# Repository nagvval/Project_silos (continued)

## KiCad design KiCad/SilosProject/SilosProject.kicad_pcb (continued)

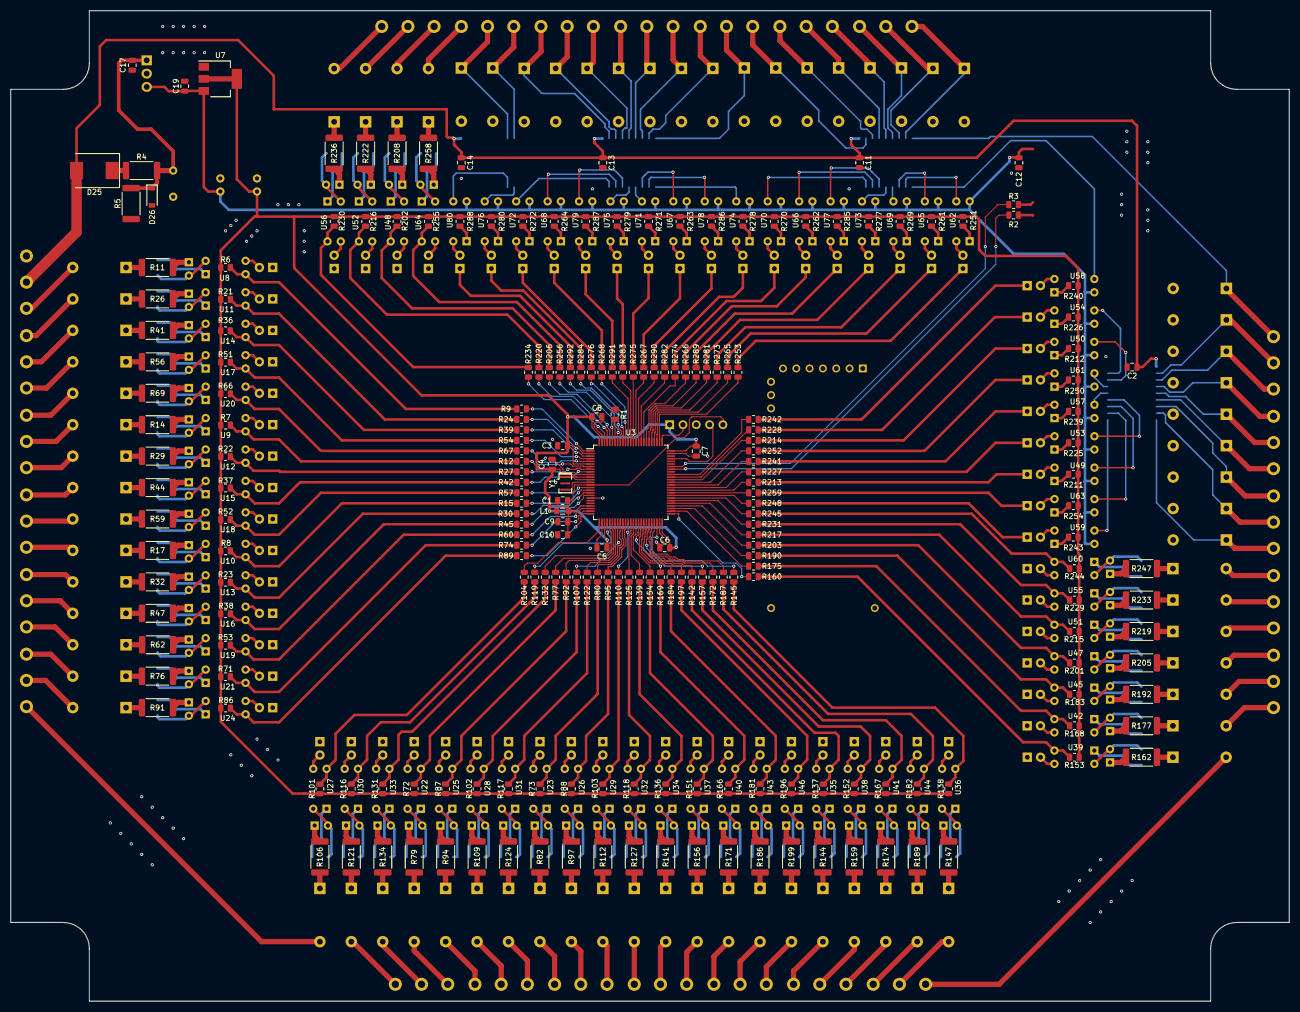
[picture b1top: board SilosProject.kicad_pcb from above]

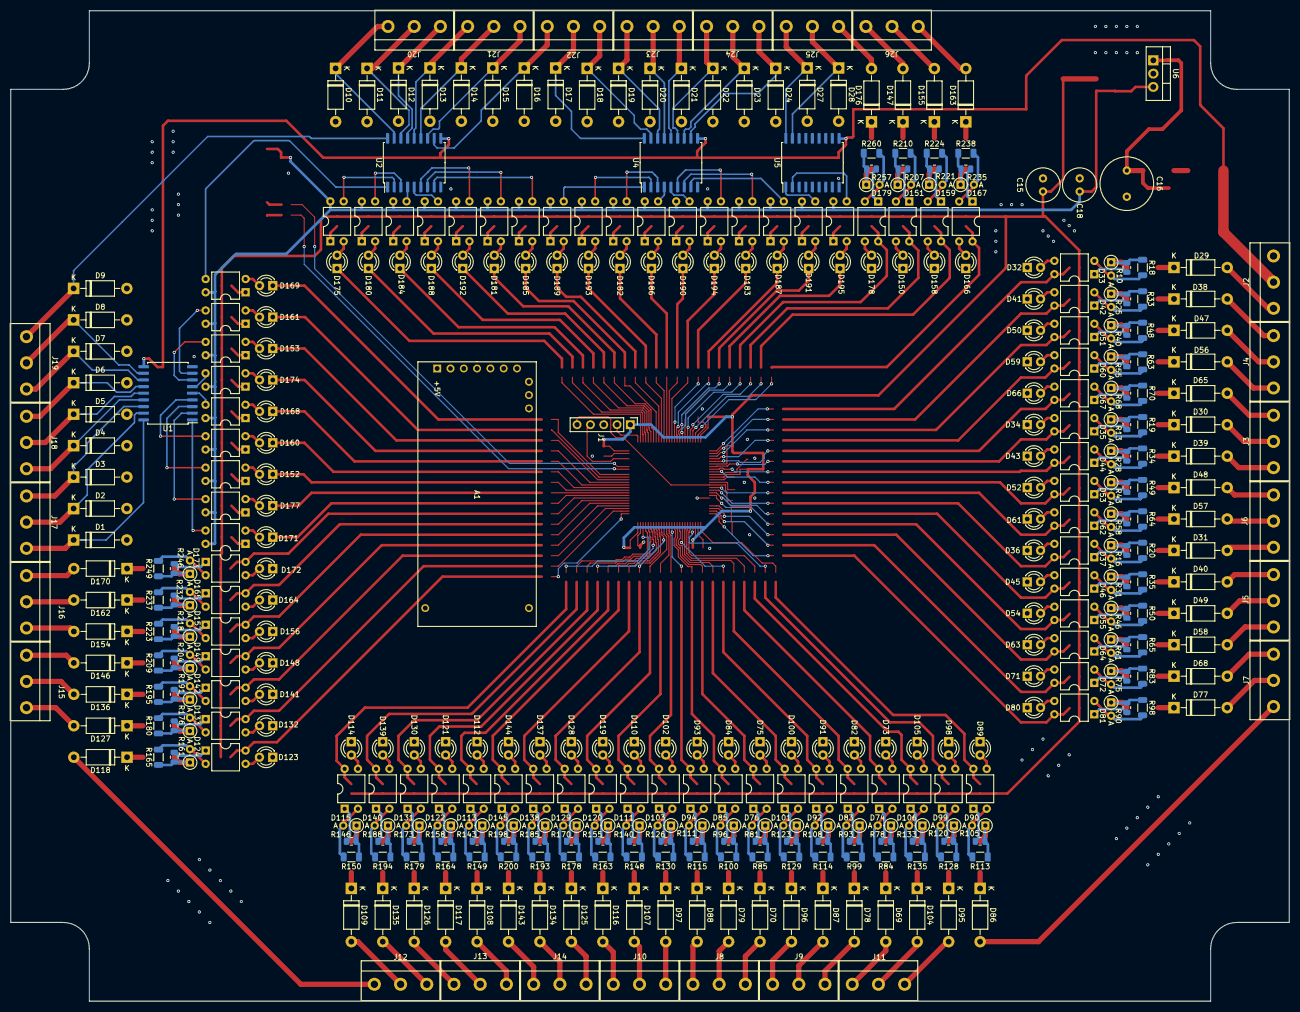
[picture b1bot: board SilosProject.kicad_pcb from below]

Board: 2 copper layers, 244.0 x 189.0 mm, 615 parts (395 on the bottom side), 548 nets.

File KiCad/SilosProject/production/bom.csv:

Designator,Footprint,Quantity,Value,LCSC Part #
A1,USR-TCP232-T2_MODUL,1,USR-TCP232-T2,
"C1, C11, C12, C13, C14, C17, C19, C2, C4, C5, C6, C7, C8",C_0805_2012Metric,13,100nF,
C10,C_0805_2012Metric,1,10nF,
C15,C_Radial_D6.3mm_H11.0mm_P2.50mm,1,"220uF, 10V",
C16,C_Radial_D10.0mm_H12.5mm_P5.00mm,1,220uF 50V,
C18,C_Radial_D6.3mm_H11.0mm_P2.50mm,1,220uF 25V,
C3,C_0805_2012Metric,1,4.7uF,
C9,C_0805_2012Metric,1,1uF,
"D1, D10, D104, D107, D108, D109, D11, D116, D117, D118, D12, D125, D126, D127, D13, D134, D135, D136, D14, D143, D146, D147, D15, D154, D155, D16, D162, D163, D17, D170, D176, D18, D19, D2, D20, D21, D22, D23, D24, D27, D28, D29, D3, D30, D31, D38, D39, D4, D40, D47, D48, D49, D5, D56, D57, D58, D6, D65, D68, D69, D7, D70, D77, D78, D79, D8, D86, D87, D88, D9, D95, D96, D97",D_DO-41_SOD81_P10.16mm_Horizontal,73,1N4007,
"D100, D102, D105, D110, D112, D114, D119, D121, D123, D128, D130, D132, D137, D139, D141, D144, D148, D150, D152, D153, D156, D158, D160, D161, D164, D166, D168, D169, D171, D172, D174, D175, D177, D178, D180, D181, D182, D183, D184, D185, D186, D187, D188, D189, D190, D191, D192, D193, D194, D195, D32, D34, D36, D41, D43, D45, D50, D52, D54, D59, D61, D63, D66, D73, D75, D80, D82, D84, D89, D91, D93, D98",LED_D3.0mm,72,LED_GREEN_3mm,
"D101, D103, D106, D111, D113, D115, D120, D122, D124, D129, D131, D133, D138, D140, D142, D145, D149, D151, D157, D159, D165, D167, D173, D179, D33, D35, D37, D42, D44, D46, D51, D53, D55, D60, D62, D64, D67, D72, D74, D76, D81, D83, D85, D90, D92, D94, D99",D_DO-35_SOD27_P2.54mm_Vertical_AnodeUp,47,BZX55-C5V1,
D25,D_SMC,1,S5M,
D26,D_SOD-123,1,BZX55-C7V5,
D71,LED_D3.0mm_IRBlack,1,IR204A,
J1,PinHeader_1x05_P2.54mm_Vertical,1,Screw_Terminal_01x05,
J10,DG306-5.0-03P-12-00A,1,PORT10,
J11,DG306-5.0-03P-12-00A,1,PORT07,
J12,DG306-5.0-03P-12-00A,1,PORT13,
J13,DG306-5.0-03P-12-00A,1,PORT12,
J14,DG306-5.0-03P-12-00A,1,PORT11,
J15,DG306-5.0-03P-12-00A,1,PORT14,
J16,DG306-5.0-03P-12-00A,1,PORT15,
J17,DG306-5.0-03P-12-00A,1,PORT16,
J18,DG306-5.0-03P-12-00A,1,PORT17,
J19,DG306-5.0-03P-12-00A,1,PORT18,
J2,DG306-5.0-03P-12-00A,1,PORT01,
J20,DG306-5.0-03P-12-00A,1,PORT19,
J21,DG306-5.0-03P-12-00A,1,PORT20,
J22,DG306-5.0-03P-12-00A,1,PORT21,
J23,DG306-5.0-03P-12-00A,1,PORT22,
J24,DG306-5.0-03P-12-00A,1,PORT23,
J25,DG306-5.0-03P-12-00A,1,PORT24,
J26,DG306-5.0-03P-12-00A,1,PORT25,
J3,DG306-5.0-03P-12-00A,1,PORT03,
J4,DG306-5.0-03P-12-00A,1,PORT02,
J5,DG306-5.0-03P-12-00A,1,PORT05,
J6,DG306-5.0-03P-12-00A,1,PORT04,
J7,DG306-5.0-03P-12-00A,1,PORT06,
J8,DG306-5.0-03P-12-00A,1,PORT09,
J9,DG306-5.0-03P-12-00A,1,PORT08,
L1,L_0805_2012Metric_Pad1.05x1.20mm_HandSolder,1,100MHz-600,
R1,C_0805_2012Metric,1,10K,
"R10, R105, R108, R111, R120, R123, R126, R13, R133, R140, R143, R146, R155, R158, R16, R161, R170, R173, R176, R185, R188, R191, R198, R204, R207, R218, R221, R232, R235, R246, R25, R257, R28, R31, R40, R43, R46, R55, R58, R61, R68, R75, R78, R81, R90, R93, R96",R_0805_2012Metric,47,200,
"R100, R113, R114, R115, R128, R129, R130, R135, R148, R149, R150, R163, R164, R165, R178, R179, R18, R180, R19, R193, R194, R195, R20, R200, R209, R210, R223, R224, R237, R238, R249, R260, R33, R34, R35, R48, R49, R50, R63, R64, R65, R70, R83, R84, R85, R98, R99",R_1206_3216Metric,47,3.3K,
"R101, R102, R103, R116, R117, R118, R131, R136, R137, R138, R151, R152, R153, R166, R167, R168, R181, R182, R183, R196, R201, R202, R21, R215, R216, R22, R229, R23, R230, R244, R255, R36, R37, R38, R51, R52, R53, R6, R66, R7, R71, R72, R73, R8, R86, R87, R88",R_0805_2012Metric,47,10K,
"R104, R107, R110, R119, R12, R122, R125, R132, R139, R142, R145, R15, R154, R157, R160, R169, R172, R175, R184, R187, R190, R197, R2, R203, R206, R213, R214, R217, R220, R227, R228, R231, R234, R24, R241, R242, R245, R248, R252, R253, R256, R259, R265, R266, R267, R268, R27, R273, R274, R275, R276, R281, R282, R283, R284, R289, R290, R291, R292, R3, R30, R39, R42, R45, R54, R57, R60, R67, R74, R77, R80, R89, R9, R92, R95",R_0805_2012Metric,75,0,
"R106, R109, R11, R112, R121, R124, R127, R134, R14, R141, R144, R147, R156, R159, R162, R17, R171, R174, R177, R186, R189, R192, R199, R205, R208, R219, R222, R233, R236, R247, R258, R26, R29, R32, R41, R44, R47, R56, R59, R62, R69, R76, R79, R82, R91, R94, R97",R_2512_6332Metric,47,10K,
"R211, R212, R225, R226, R239, R240, R243, R250, R251, R254, R261, R262, R263, R264, R269, R270, R271, R272, R277, R278, R279, R280, R285, R286, R287, R288",R_0805_2012Metric,26,1K,
R4,R_2512_6332Metric,1,100K,
R5,R_2512_6332Metric,1,47K,
"U1, U2, U4, U5",SOIC-18W_7.5x11.6mm_P1.27mm,4,ULN2803A,
"U10, U11, U12, U13, U14, U15, U16, U17, U18, U19, U20, U21, U22, U23, U24, U25, U26, U27, U28, U29, U30, U31, U32, U33, U34, U35, U36, U37, U38, U39, U40, U41, U42, U43, U44, U45, U46, U47, U48, U51, U52, U55, U56, U60, U64, U8, U9",DIP-4_W7.62mm,47,EL817,
U3,LQFP-100_14x14mm_P0.5mm,1,STM32F100VETx,
"U49, U50, U53, U54, U57, U58, U59, U61, U62, U63, U65, U66, U67, U68, U69, U70, U71, U72, U73, U74, U75, U76, U77, U78, U79, U80",DIP-4_W7.62mm,26,PC817,
U6,TO-220-3_Vertical,1,L7805,
U7,SOT-223-3_TabPin2,1,LD1117S33TR_SOT223,
Y1,Resonator_SMD_Murata_CSTxExxV-3Pin_3.0x1.1mm,1,8MHz,

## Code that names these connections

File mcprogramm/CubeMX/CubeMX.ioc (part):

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Mcu.Name=STM32F100V(C-D-E)Tx
Mcu.Package=LQFP100
Mcu.UserName=STM32F100VETx
PA0-WKUP.GPIOParameters=GPIO_Label
PA0-WKUP.GPIO_Label=SUM M3
PA0-WKUP.Signal=GPIO_Input
PA1.GPIOParameters=GPIO_Label
PA1.GPIO_Label=SUM M5
PA1.Signal=GPIO_Input
PA10.Mode=Asynchronous
PA10.Signal=USART1_RX
PA13.Signal=SYS_JTMS-SWDIO
PA14.Signal=SYS_JTCK-SWCLK
PA15.GPIOParameters=GPIO_Label
PA15.GPIO_Label=Play M9 Forvard
PA15.Signal=GPIO_Output
PA2.GPIOParameters=GPIO_Label
PA2.GPIO_Label=SUM M6
PA2.Signal=GPIO_Input
PA3.GPIOParameters=GPIO_Label
PA3.GPIO_Label=SUM M7
PA3.Signal=GPIO_Input
PA4.GPIOParameters=GPIO_Label
PA4.GPIO_Label=SUM M8
PA4.Signal=GPIO_Input
PA5.GPIOParameters=GPIO_Label
PA5.GPIO_Label=SUM M9 Forvard
PA5.Signal=GPIO_Input
PA6.GPIOParameters=GPIO_Label
PA6.GPIO_Label=SUM M9 Revers
PA6.Signal=GPIO_Input
PA7.GPIOParameters=GPIO_Label
PA7.GPIO_Label=Silos level 1 (Low)
PA7.Signal=GPIO_Input
PA9.Mode=Asynchronous
PA9.Signal=USART1_TX
PB0.GPIOParameters=GPIO_Label
PB0.GPIO_Label=Silos level 4
PB0.Signal=GPIO_Input
PB1.GPIOParameters=GPIO_Label
PB1.GPIO_Label=Silos level 5 (High)
PB1.Signal=GPIO_Input
PB10.GPIOParameters=GPIO_Label
PB10.GPIO_Label=Thermal M7
PB10.Signal=GPIO_Input
PB11.GPIOParameters=GPIO_Label
PB11.GPIO_Label=Thermal M8
PB11.Signal=GPIO_Input
PB12.GPIOParameters=GPIO_Label
PB12.GPIO_Label=Thermal M9
PB12.Signal=GPIO_Input
PB13.GPIOParameters=GPIO_Label
PB13.GPIO_Label=Thermal M10
PB13.Signal=GPIO_Input
PB14.GPIOParameters=GPIO_Label
PB14.GPIO_Label=Thermal M11
PB14.Signal=GPIO_Input
PB15.GPIOParameters=GPIO_Label
PB15.GPIO_Label=Thermal M12
PB15.Signal=GPIO_Input
PB2.GPIOParameters=GPIO_Label
PB2.GPIO_Label=Boiler level Low
PB2.Signal=GPIO_Input
PB3.GPIOParameters=GPIO_Label
PB3.GPIO_Label=Lamp M8
PB3.Signal=GPIO_Output
PB4.GPIOParameters=GPIO_Label
PB4.GPIO_Label=Lamp M9
PB4.Signal=GPIO_Output
PB5.GPIOParameters=GPIO_Label
PB5.GPIO_Label=Lamp M10
PB5.Signal=GPIO_Output
PB6.GPIOParameters=GPIO_Label
PB6.GPIO_Label=Lamp M11
PB6.Signal=GPIO_Output
PB7.GPIOParameters=GPIO_Label
PB7.GPIO_Label=Lamp M12
PB7.Signal=GPIO_Output
PB8.GPIOParameters=GPIO_Label
PB8.GPIO_Label=Auto Boiler Basic
PB8.Signal=GPIO_Input
PB9.GPIOParameters=GPIO_Label
PB9.GPIO_Label=Auto Boiler Reserv
PB9.Signal=GPIO_Input
PC0.GPIOParameters=GPIO_Label
PC0.GPIO_Label=Button M8
PC0.Signal=GPIO_Input
PC1.GPIOParameters=GPIO_Label
PC1.GPIO_Label=Button M9 Forvard
PC1.Signal=GPIO_Input
PC10.GPIOParameters=GPIO_Label
PC10.GPIO_Label=Play M9 Revers
PC10.Signal=GPIO_Output
PC11.GPIOParameters=GPIO_Label
PC11.GPIO_Label=Play M10
PC11.Signal=GPIO_Output
PC12.GPIOParameters=GPIO_Label
PC12.GPIO_Label=Play M11
PC12.Signal=GPIO_Output
PC13-TAMPER-RTC.GPIOParameters=GPIO_Label
PC13-TAMPER-RTC.GPIO_Label=Button M5
PC13-TAMPER-RTC.Signal=GPIO_Input
PC14-OSC32_IN.GPIOParameters=GPIO_Label
PC14-OSC32_IN.GPIO_Label=Button M6
PC14-OSC32_IN.Signal=GPIO_Input
PC15-OSC32_OUT.GPIOParameters=GPIO_Label
PC15-OSC32_OUT.GPIO_Label=Button M7
PC15-OSC32_OUT.Signal=GPIO_Input
PC2.GPIOParameters=GPIO_Label
PC2.GPIO_Label=Button M9 Revers
PC2.Signal=GPIO_Input
PC3.GPIOParameters=GPIO_Label
PC3.GPIO_Label=Button M10, M11, M12
PC3.Signal=GPIO_Input
PC4.GPIOParameters=GPIO_Label
PC4.GPIO_Label=Silos level 2
PC4.Signal=GPIO_Input
PC5.GPIOParameters=GPIO_Label
PC5.GPIO_Label=Silos level 3
PC5.Signal=GPIO_Input
PC6.GPIOParameters=GPIO_Label
PC6.GPIO_Label=Play M5
PC6.Signal=GPIO_Output
PC7.GPIOParameters=GPIO_Label
PC7.GPIO_Label=Play M6
PC7.Signal=GPIO_Output
PC8.GPIOParameters=GPIO_Label
PC8.GPIO_Label=Play M7
PC8.Signal=GPIO_Output
PC9.GPIOParameters=GPIO_Label
PC9.GPIO_Label=Play M8
PC9.Signal=GPIO_Output
PD0.GPIOParameters=GPIO_Label
PD0.GPIO_Label=Play M12
PD0.Signal=GPIO_Output
PD1.GPIOParameters=GPIO_Label
PD1.GPIO_Label=Lamp M1
PD1.Signal=GPIO_Output
PD10.GPIOParameters=GPIO_Label
PD10.GPIO_Label=Gotvald signal door
PD10.Signal=GPIO_Input
PD11.GPIOParameters=GPIO_Label
PD11.GPIO_Label=Lamp STOP
PD11.Signal=GPIO_Output
PD12.GPIOParameters=GPIO_Label
PD12.GPIO_Label=Play M1
PD12.Signal=GPIO_Output
PD13.GPIOParameters=GPIO_Label
PD13.GPIO_Label=Play M2
PD13.Signal=GPIO_Output
PD14.GPIOParameters=GPIO_Label
PD14.GPIO_Label=Play M3
PD14.Signal=GPIO_Output
PD15.GPIOParameters=GPIO_Label
PD15.GPIO_Label=Play M4
PD15.Signal=GPIO_Output
PD2.GPIOParameters=GPIO_Label
PD2.GPIO_Label=Lamp M2
PD2.Signal=GPIO_Output
PD3.GPIOParameters=GPIO_Label
PD3.GPIO_Label=Lamp M3
PD3.Signal=GPIO_Output
PD4.GPIOParameters=GPIO_Label
PD4.GPIO_Label=Lamp M4
PD4.Signal=GPIO_Output
PD5.GPIOParameters=GPIO_Label
PD5.GPIO_Label=Lamp M5
PD5.Signal=GPIO_Output
PD6.GPIOParameters=GPIO_Label
PD6.GPIO_Label=Lamp M6
PD6.Signal=GPIO_Output
PD7.GPIOParameters=GPIO_Label
PD7.GPIO_Label=Lamp M7
PD7.Signal=GPIO_Output
PD8.GPIOParameters=GPIO_Label
PD8.GPIO_Label=Vibrator signal
PD8.Signal=GPIO_Input
PD9.GPIOParameters=GPIO_Label
PD9.GPIO_Label=Gotvald Signal switch M1
PD9.Signal=GPIO_Input
PE0.GPIOParameters=GPIO_Label
PE0.GPIO_Label=Auto Pillet Basic
PE0.Signal=GPIO_Input
PE1.GPIOParameters=GPIO_Label
PE1.GPIO_Label=Auto Pillet Reserv
PE1.Signal=GPIO_Input
PE10.GPIOParameters=GPIO_Label
PE10.GPIO_Label=Thermal M1
PE10.Signal=GPIO_Input
PE11.GPIOParameters=GPIO_Label
PE11.GPIO_Label=Thermal M2
PE11.Signal=GPIO_Input
PE12.GPIOParameters=GPIO_Label
PE12.GPIO_Label=Thermal M3
PE12.Signal=GPIO_Input
PE13.GPIOParameters=GPIO_Label
PE13.GPIO_Label=Thermal M4
PE13.Signal=GPIO_Input
PE14.GPIOParameters=GPIO_Label
PE14.GPIO_Label=Thermal M5
PE14.Signal=GPIO_Input
PE15.GPIOParameters=GPIO_Label
PE15.GPIO_Label=Thermal M6
PE15.Signal=GPIO_Input
PE2.GPIOParameters=GPIO_Label
PE2.GPIO_Label=Button STOP
PE2.Signal=GPIO_Input
PE3.GPIOParameters=GPIO_Label
PE3.GPIO_Label=Button M1
PE3.Signal=GPIO_Input
PE4.GPIOParameters=GPIO_Label
PE4.GPIO_Label=Button M2
PE4.Signal=GPIO_Input
PE5.GPIOParameters=GPIO_Label
PE5.GPIO_Label=Button M3
PE5.Signal=GPIO_Input
PE6.GPIOParameters=GPIO_Label
PE6.GPIO_Label=Button M4
PE6.Signal=GPIO_Input
PE7.GPIOParameters=GPIO_Label
PE7.GPIO_Label=Boiler Level High
PE7.Signal=GPIO_Input
PE8.GPIOParameters=GPIO_Label
PE8.GPIO_Label=Pillet level Low
PE8.Signal=GPIO_Input
PE9.GPIOParameters=GPIO_Label
PE9.GPIO_Label=Pillet level High
PE9.Signal=GPIO_Input
board=custom

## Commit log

2023-03-15 first upload
2023-03-15 add README file
2023-03-15 port D11 experement
2023-03-20 Experement input E2
